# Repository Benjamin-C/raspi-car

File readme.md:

Raspberry Pi Controlled Little Car
===

This project is to create a small car that can drive around semi-autonomously. It has several cameras that can be used for computer vision or automated measurements, all controlled by a Raspberry Pi.

# Components
1. [Hiwonder Mecanum Wheel Chassis Car Kit](https://www.hiwonder.com/products/mecanum-wheel-chassis-car)
2. [Raspberry Pi 5 8GB](https://www.raspberrypi.com/products/raspberry-pi-5/)
3. [OAK-D Lite Sterioscopic Camera](https://shop.luxonis.com/collections/oak-cameras-1/products/oak-d-lite-1)
4. [Infaray P2 Pro thermal camera](https://www.infiray.com/p2-pro-thermal-camera-for-smartphone/)
5. [Sodium Ion 18650 Batteries](https://srikobatteries.com/product/sodium-ion-18650-3-0v-1-3ah-3-90wh-10c-rechargeable-battery/?srsltid=AfmBOoqf1Pw8MhQu-_pQYGnII_iEBP2QReIwijq0zAHCvC58VseaeiDhdz4)
6. 3d printed camera bracket
7. Car control PCB

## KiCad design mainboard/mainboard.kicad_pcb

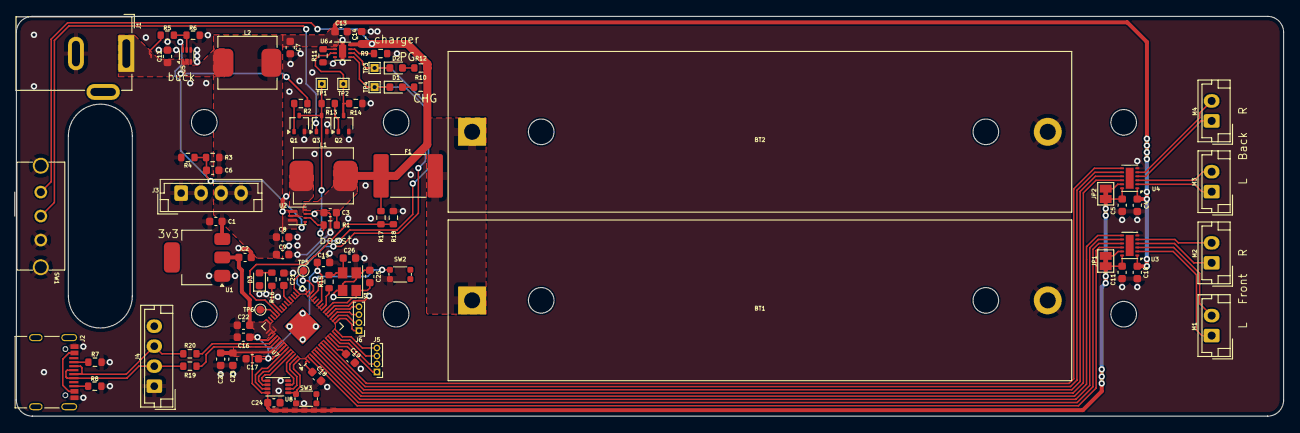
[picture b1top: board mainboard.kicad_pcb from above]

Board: 2 copper layers, 158.5 x 50.0 mm, 87 parts (0 on the bottom side), 70 nets.

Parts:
BT1, BT2: Na-Ion; BatteryHolder_MPD_BH-18650-PC2
C1, C5, C6, C11, C15, C16, C18, C19, C20, C21, C22, C23: 0.1u; C_0603_1608Metric
C2, C7, C8, C9, C24: 22u; C_0603_1608Metric
C3, C4, C10, C12: 10u; C_0603_1608Metric
C13, C14: 1u; C_0603_1608Metric
C17: 2.2u; C_0603_1608Metric
C25, C26: C_XTL; C_0603_1608Metric
D1, D2: LED; LED_0603_1608Metric
D3: LED_GREEN; LED_0603_1608Metric
F1: 7A Poly; Fuse_2920_7451Metric
J1: Barrel_Jack; BarrelJack_GCT_DCJ200-10-A_Horizontal
J2: USB_C_Receptacle_USB2.0_14P; USB_C_Receptacle_USB2
J3, J4: Conn_01x04; JST_EH_B4B-EH-A_1x04_P2.50mm_Vertical
J5, J6: Conn_01x04; PinHeader_1x04_P1.00mm_Vertical
JP1, JP2: Jumper_2_Bridged; SolderJumper-2_P1.3mm_Bridged_Pad1.0x1.5mm
L1: 750n; inductor_PA431
L2: 2.2u; inductor_BMRx
M1, M2, M3, M4: Motor_DC; JST_EH_B2B-EH-A_1x02_P2.50mm_Vertical
Q1, Q2, Q3: 2N7002; SOT-323_SC-70
R1, R6, R10, R12, R14, R17, R18: 10k; R_0603_1608Metric
R2, R13, R15: 1k; R_0603_1608Metric
R3: 732k; R_0603_1608Metric
R4: 100k; R_0603_1608Metric
R5: 33k; R_0603_1608Metric
R7, R8: 5k1; R_0603_1608Metric
R9: 62k; R_0603_1608Metric
R11: 374; R_0603_1608Metric
R16: 4k7; R_0603_1608Metric
R19, R20: 27; R_0603_1608Metric
SW1: SW_SPDT
SW2, SW3: SW_SPST; SW_SPST_2.8x1.9
TP1, TP2, TP3, TP4: TestPoint_Small; TestPoint_THTPad_1.0x1.0mm_Drill0.5mm
TP5, TP6: TestPoint; TestPoint_Pad_D1.0mm
U1: AMS1117-3.3; SOT-223-3_TabPin2
U2: TPS61022RWUR; VQFN-7
U3, U4: DRV8835; WSON-12-1EP_3x2mm_P0.5mm_EP1x2.65
U5: TPS566242DRLR; SOT-563
U6: BQ25170; WSON-8-1EP_2x2mm_P0.5mm_EP0.9x1.6mm
U7: RP2040; QFN-56-1EP_7x7mm_P0.4mm_EP3.2x3.2mm
U8: W25Q16JVUXIQ TR; 8-UFDFN
Y1: 12MHz; Crystal_SMD_3225-4Pin_3.2x2.5mm

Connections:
+1V1: C15.1, C16.1, C17.1, U7.23 (DVDD), U7.45 (VREG_VOUT), U7.50 (DVDD)
+3V3: C2.1, C5.1, C11.1, C18.1, C19.1, C20.1, C21.1, C22.1, C23.1, C24.2, JP1.1 (A), JP2.1 (A), U1.2 (VO), U3.12 (VCC), U4.12 (VCC), U7.1 (IOVDD), U7.10 (IOVDD), U7.22 (IOVDD), U7.33 (IOVDD), U7.42 (IOVDD), U7.43 (ADC_AVDD), U7.44 (VREG_IN), U7.48 (USB_VDD), U7.49 (IOVDD), U8.8 (Vcc)
+5V: C1.1, C4.1, C6.1, C7.1, C8.1, C9.1, C10.1, C13.1, J3.3, J3.4, L2.2, R3.1, U1.3 (VI), U2.3 (VOUT), U3.1 (VMOT), U4.1 (VMOT), U6.1 (IN)
/CHG_DISABLE: Q2.3 (D), R14.1, TP2.1, U6.3 (TS)
/DISCH_DISABLE: Q3.1 (G), SW1.2 (B)
/Microcontroller/QSPI_CS: SW3.1 (A), U7.56 (QSPI_SS), U8.1 (~cs)
/Microcontroller/QSPI_SCLK: U7.52 (QSPI_SCLK), U8.6 (CLK)
/Microcontroller/QSPI_SD0: U7.53 (QSPI_SD0), U8.5 (Dio0)
/Microcontroller/QSPI_SD1: U7.55 (QSPI_SD1), U8.2 (Dio1)
/Microcontroller/QSPI_SD2: U7.54 (QSPI_SD2), U8.3 (Dio2)
/Microcontroller/QSPI_SD3: U7.51 (QSPI_SD3), U8.7 (Dio3)
/Microcontroller/XIN: C25.1, U7.20 (XIN), Y1.1
/Microcontroller/XOUT: R15.2, U7.21 (XOUT)
/Microcontroller/XR: C26.1, R15.1, Y1.3
/vreg_feedback: C6.2, R3.2, R4.1, U2.4 (FB), U5.6 (FB)
CHG_PG: D2.1 (K), TP3.1, U6.6 (~PG), U7.28 (GPIO17)
CHG_STAT: D1.1 (K), TP4.1, U6.5 (STAT), U7.27 (GPIO16)
GND: BT1.2 (-), BT2.2 (-), C1.2, C2.2, C3.2, C4.2, C5.2, C7.2, C8.2, C9.2, C10.2, C11.2, C12.2, C13.2, C14.2, C15.2, C16.2, C17.2, C18.2, C19.2, C20.2, C21.2, C22.2, C23.2, C24.1, C25.2, C26.2, D3.1 (K), J1.2, J2.A1 (GND), J2.A12 (GND), J2.B1 (GND), J2.B12 (GND), J3.1, J3.2, J4.1, Q1.2 (S), Q2.2 (S), Q3.2 (S), R4.2, R6.2, R7.2, R8.2, R9.1, R11.2, R14.2, R18.2, SW1.3 (C), SW1.M, SW2.2 (B), SW3.2 (B), U1.1 (GND), U2.1 (Gnd), U2.6 (Mode), U3.6 (GND), U4.6 (GND), U5.3 (GND), U5.4 (AGND), U6.4 (GND), U6.9 (PAD), U7.19 (TESTEN), U7.57 (GND), U8.4 (GND), Y1.2, Y1.4
MOTA_DIR: U3.10 (APh), U7.2 (GPIO0)
MOTA_PWM: U3.9 (Aen), U7.3 (GPIO1)
MOTB_DIR: U3.8 (BPh), U7.4 (GPIO2)
MOTB_PWM: U3.7 (BEn), U7.5 (GPIO3)
MOTC_DIR: U4.10 (APh), U7.6 (GPIO4)
MOTC_PWM: U4.9 (Aen), U7.7 (GPIO5)
MOTD_DIR: U4.8 (BPh), U7.8 (GPIO6)
MOTD_PWM: U4.7 (BEn), U7.9 (GPIO7)
unnamed: BT1.1 (+), BT2.1 (+), F1.2
unnamed: D1.2 (A), R10.1
unnamed: D2.2 (A), R12.1
unnamed: D3.2 (A), R16.1
unnamed: J2.A5 (CC1), R7.1
unnamed: J2.B5 (CC2), R8.1
unnamed: J5.1, U7.11 (GPIO8)
unnamed: J5.2, U7.12 (GPIO9)
unnamed: J5.3, U7.13 (GPIO10)
unnamed: J5.4, U7.14 (GPIO11)
unnamed: J6.1, U7.15 (GPIO12)
unnamed: J6.2, U7.16 (GPIO13)
unnamed: J6.3, U7.17 (GPIO14)
unnamed: J6.4, U7.18 (GPIO15)
unnamed: JP1.2 (B), U3.11 (Mode)
unnamed: JP2.2 (B), U4.11 (Mode)
unnamed: M1.1 (+), U3.2 (AOUT1)
unnamed: M1.2 (-), U3.3 (AOUT2)
unnamed: M2.1 (+), U3.4 (BOUT1)
unnamed: M2.2 (-), U3.5 (BOUT2)
unnamed: M3.1 (+), U4.2 (AOUT1)
unnamed: M3.2 (-), U4.3 (AOUT2)
unnamed: M4.1 (+), U4.4 (BOUT1)
unnamed: M4.2 (-), U4.5 (BOUT2)
unnamed: Q1.1 (G), R2.1
unnamed: Q2.1 (G), R13.2
unnamed: SW2.1 (A), U7.26 (RUN)
unnamed: L1.2, U2.2 (SW)
unnamed: R5.2, R6.1, U5.5 (EN)
unnamed: L2.1, U5.2 (SW)
unnamed: R11.1, U6.2 (ISET)
unnamed: R9.2, U6.7 (VSET)
unnamed: TP5.1, U7.29 (GPIO18)
unnamed: R16.2, U7.37 (GPIO25)
unnamed: R17.2, R18.1, U7.38 (GPIO26_ADC0)
unnamed: TP6.1, U7.39 (GPIO27_ADC1)
unnamed: R20.2, U7.46 (USB_DM)
unnamed: R19.2, U7.47 (USB_DP)
PWR_BATT: Q1.3 (D), Q3.3 (D), R1.2, R13.1, TP1.1, U2.5 (En)
USB_D+: J2.A6 (D+), J2.B6 (D+), J4.2, R19.1
USB_D-: J2.A7 (D-), J2.B7 (D-), J4.3, R20.1
VBAT: C3.1, C14.1, F1.1, L1.1, R1.1, R10.2, R12.2, R17.1, SW1.1 (A), U2.7 (Vin), U6.8 (OUT)
VIN: C12.1, J1.1, R2.2, R5.1, U5.1 (Vin)
VUSB: J2.A4 (VBUS), J2.A9 (VBUS), J2.B4 (VBUS), J2.B9 (VBUS)

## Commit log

2024-04-30 init
2024-04-30 Prepared for PCB layout
2024-05-06 Added some 3d libs and started routing
2024-05-07 More building
2024-05-07 Finished routing
2024-05-07 Trace Edits
2024-05-15 Added demo joystick
2024-05-15 Added Python code
2024-05-15 Added camera files
2024-05-15 Moved things to car lib
2024-06-10 Added mainboard firmware
2024-06-17 Added .gitignore
2024-06-17 Added mainbord comms
2024-06-17 Added stop command
2024-06-17 Updated for real hardware
2024-06-17 Fixed serial bugs
2024-06-17 Added delays if desired
2024-06-17 Fixed encoding
2024-06-17 Added more drive commands
2024-06-17 Hid debug messages
2024-06-17 Added new main Python file
2024-06-17 Added testing stuffs
2024-06-17 Made it dance a square
2024-06-17 Added dance example
2024-06-17 Add dance
2024-06-17 Maybe fixed dance
2024-06-17 More dance fix
2024-06-17 dance tweaked again
2024-06-17 Stop on close now
2024-06-17 Clear input buffer every write
2024-06-17 Made it sorta actually work
